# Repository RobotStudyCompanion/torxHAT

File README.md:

# torxHat

This repository contains the PCB design files for **torxHat**, designed in KiCAD, for the Robotic Study Companion (RSC; [rsc.ee](https://rsc.ee/)).
TorxHAT's design helps reduce dependency on any single specific Raspberry Pi audio HAT by supporting a wider variety. 
TorxHAT features USB Power Delivery and peripheral connectivity, including UART, multi channel PWM, I2C via Qwiic connector complete with a pass-through GPIO right-angle header.

Revision B Preview:

Pending validation testing; PCB in fabrication.

---

## Design Summary

A single USB-C PD input powers torxHAT, configured for 9V to 15V at up to 3A.
TorxHAT relies on two [LMR60440 3V to 36V, 4A, Synchronous, Buck Converters (link to datasheet)](https://www.ti.com/lit/ds/symlink/lmr60440.pdf?ts=1761834057549) powering two independent 5.1 V rails:

1. Logic rail: Raspberry Pi, audio hardware, and display
2. High-current rail for noisier peripherals: both servos, arcade button's LED plus an [Adafruit neopxLED ring (link to product page)](https://www.adafruit.com/product/2856)

TorxHAT's PCB packs a compact four-layer Raspberry Pi HAT-compatible design (though no EEPROM) with a complete pass-through GPIO connectivity intended for audio HATs.

We looked at the pinouts of following audio HATs when designing torxHAT:
* [Seeed Studios ReSpeaker 2-Mics pHAT v1.2(pinout link)](https://pinout.xyz/pinout/respeaker_2_mics_phat)
* [Waveshare WM8960 Audio HAT (product link)](https://www.waveshare.com/wm8960-audio-hat.htm)
* [Whisplay HAT(product link)](https://www.pisugar.com/products/whisplay-hat-for-pi-zero-2w-audio-display)
* [Adafruit Voice Bonnet (EOL; product link)](https://www.adafruit.com/product/4757)  
* [Google AIY Voice Bonnet v2 (EOL; pinout link)](https://pinout.xyz/pinout/aiy_voice_bonnet)
* [Google AIY Voice HAT v1 (EOL; pinout link)](https://pinout.xyz/pinout/voice_hat)

---

## Authors

* **RevA**: Raiko Torga
  * Original Bachelor's thesis artefact contribution. 
  * Supervisors: Matevž Borjan Zorec and Farnaz Baksh

* **RevB**: Raiko Torga, Matevž Borjan Zorec  

© Robot Study Companion 2026

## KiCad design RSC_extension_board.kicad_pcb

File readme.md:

# torxHat

This repository contains the PCB design files for **torxHat** developed for the Robotic Study Companion (RSC) platform.

This board was designed to reduce dependency on specific audio HATs, while supporting multiple audio HAT options it also offers USB power delivery and peripheral connectivity.

---

## Design Summary
The PCB was designed in KiCad.

The board is powered from a single USB-C PD input configured for 20 V 2.5 A.

Power distribution is split into two independent 5.1 V rails:

* Logic rail for Raspberry Pi, audio hardware, and display
* High-current rail for servos and LED ring

The PCB is a compact two-layer Raspberry Pi HAT-compatible design with pass-through GPIO connectivity intended for audio HATs.

Audio HATs considered:

* AIY Voice Bonnet  
* ReSpeaker 2 Mics pHAT  
* WM8960 Audio HAT  
* AIY Voice HAT  
* Adafruit Voice Bonnet  
* Whisplay HAT  

---

## Author

Raiko Torga

University of Tartu

Robotic Study Companion

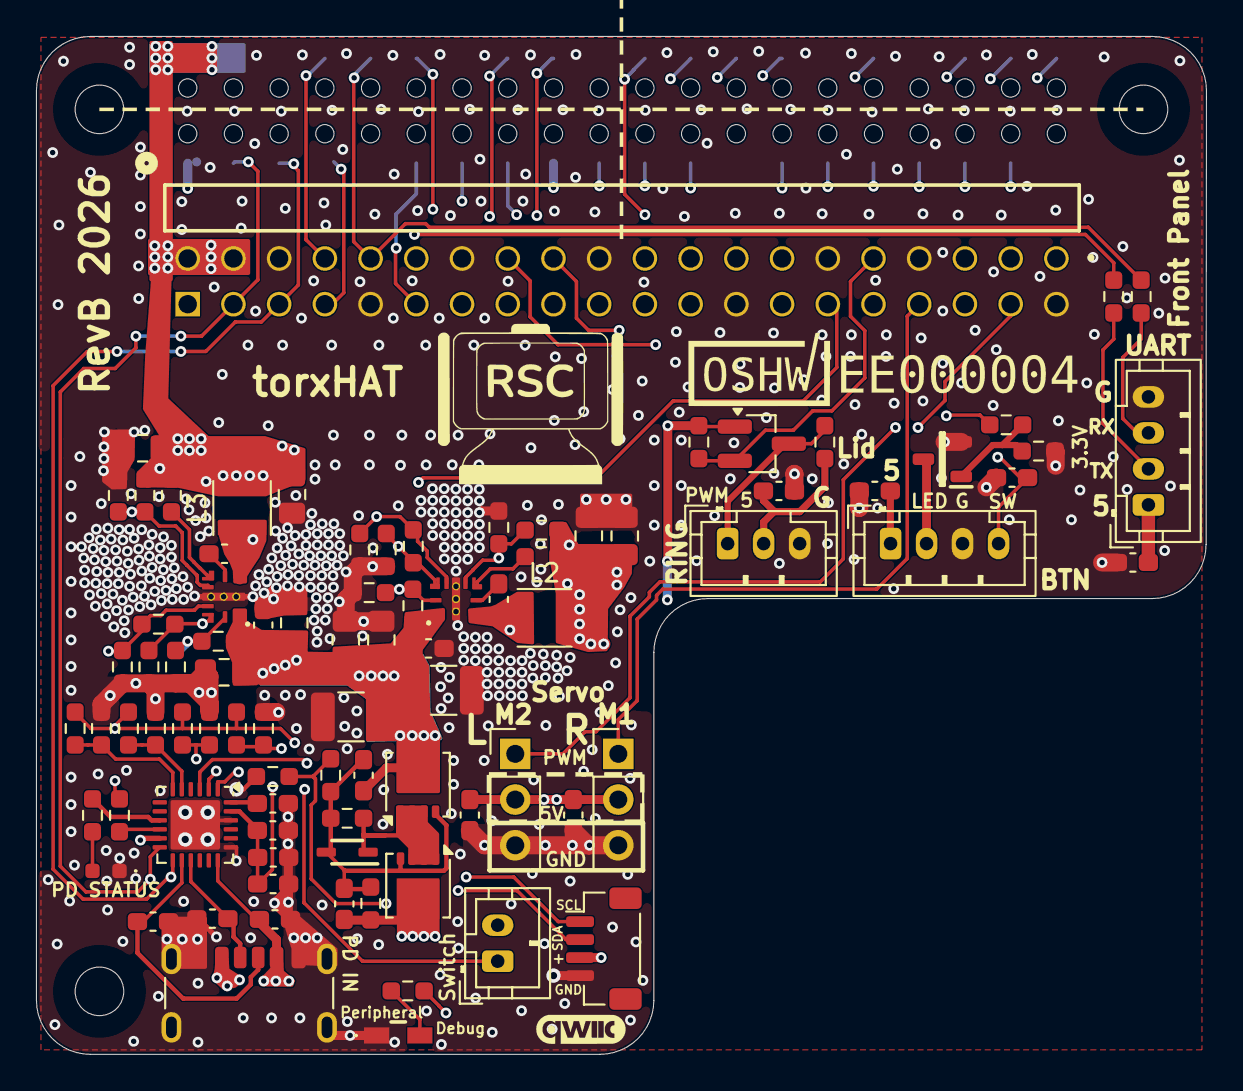
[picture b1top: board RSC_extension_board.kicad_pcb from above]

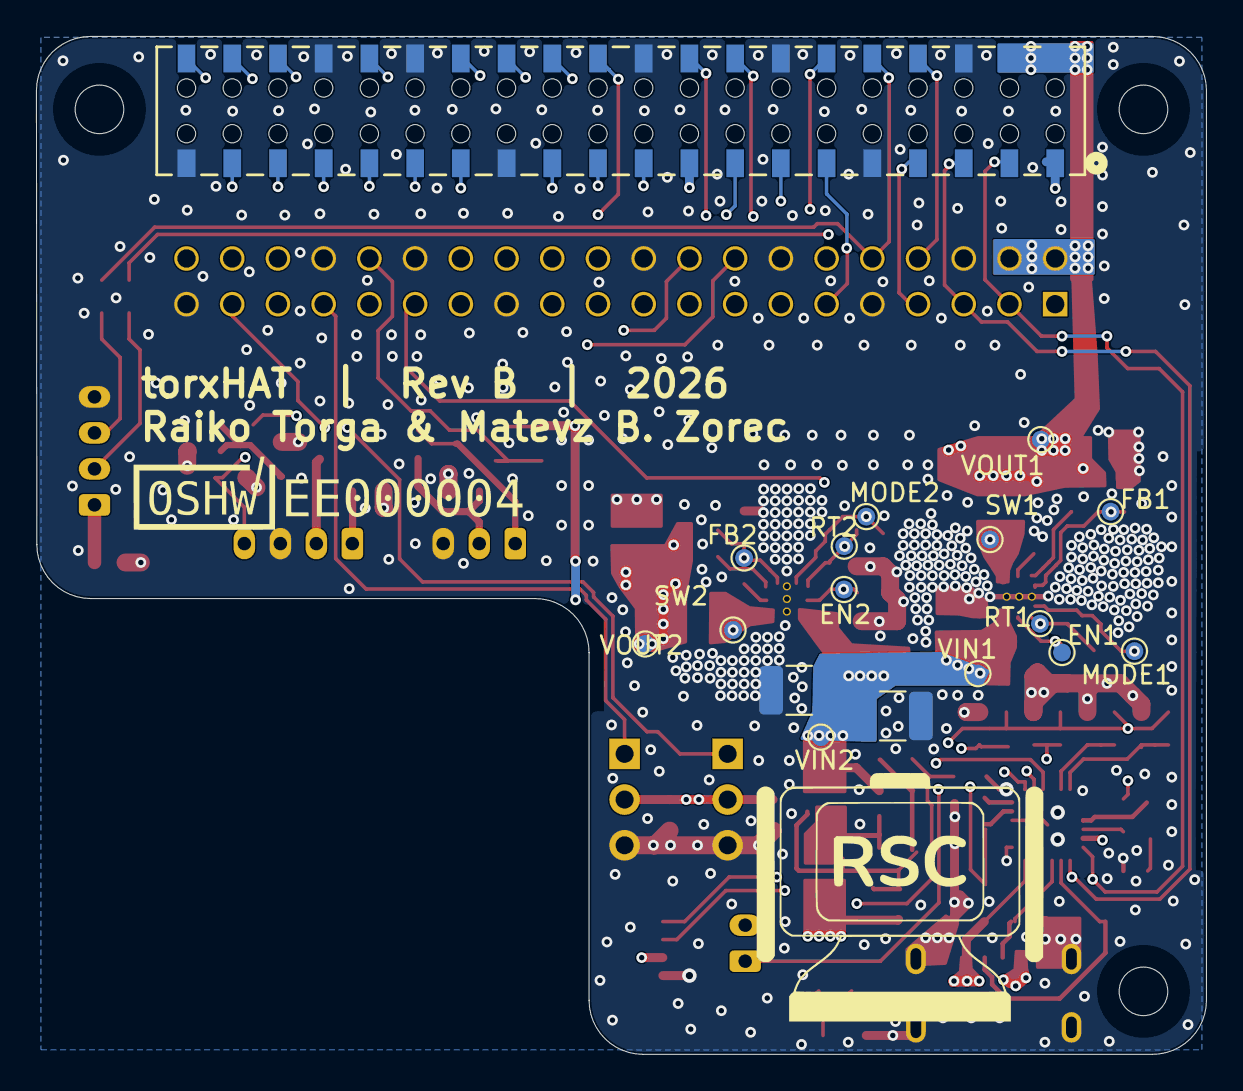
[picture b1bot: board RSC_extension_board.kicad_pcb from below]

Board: 4 copper layers, 65.0 x 56.5 mm, 105 parts (17 on the bottom side), 68 nets.

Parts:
C1, C2, C5, C6, C7, C8, C41, C42, C43, C44, C53, C54: 100nF; C_0603_1608Metric_Pad1.08x0.95mm_HandSolder
C37, C38, C39, C40: 4.7uF; C_0805_2012Metric_Pad1.18x1.45mm_HandSolder
C45, C46, C57, C58: 22uF; C_0805_2012Metric_Pad1.18x1.45mm_HandSolder
C47, C49: 390pF; C_0603_1608Metric_Pad1.08x0.95mm_HandSolder
C48: 3.3uF; C_0603_1608Metric_Pad1.08x0.95mm_HandSolder
C50, C51, C52, C55: 1uF; C_0603_1608Metric_Pad1.08x0.95mm_HandSolder
C56, C59, C60, C61: 22uF; C_1210_3225Metric_Pad1.33x2.70mm_HandSolder
D1: BAT54WS-7-F; SOD2513X120N
FPWM1, FPWM2: SHUNT; R_0603_1608Metric_Pad0.98x0.95mm_HandSolder
G1: qwiic_Logo; qwiic_5mm
J1: NPTC202KFMS-RC; CONN_NPTC202KFMS-RC_SUL
J2: Conn_01x03; JST_PH_B3B-PH-K_1x03_P2.00mm_Vertical
J3, J10: Conn_01x04; JST_PH_B4B-PH-K_1x04_P2.00mm_Vertical
J4: HTSW-120-25-L-D-RA; SAMTEC_HTSW-120-25-L-D-RA
J5: Conn_01x02; JST_PH_B2B-PH-K_1x02_P2.00mm_Vertical
J7, J8: Conn_01x03; PinHeader_1x03_P2.54mm_Vertical
J9: BM04B-SRSS; JST_SH_BM04B-SRSS-TB_1x04-1MP_P1.00mm_Vertical
J16: USB_C_Receptacle_PowerOnly_6P; USB_C_Receptacle_GCT_USB4125-xx-x-0190_6P_TopMnt_Horizontal
L2, L3: 1.5uH; L_Taiyo-Yuden_MD-3030
LED1: LW Y1SG-BFOO-GKJM-1; LWY1SGBFOOGKJM1
LED2: KR_EELP41.22-Q1S1-36-A8J8-020-R18; KREELP4122Q1S136A8J8020R18
PFM1, PFM2: DNP; R_0603_1608Metric_Pad0.98x0.95mm_HandSolder
Q1: 2N7002-7-F; SOT96P240X120-3N
Q2: BSS138; SOT-23_Handsoldering
Q3, Q4: DMP3013SFV; Diodes_PowerDI3333-8
R1, R10, R11, R22, R23: 1k; R_0603_1608Metric_Pad0.98x0.95mm_HandSolder
R2, R17: 150; R_0603_1608Metric_Pad0.98x0.95mm_HandSolder
R3, R4, R8: 10k; R_0603_1608Metric_Pad0.98x0.95mm_HandSolder
R5, R6, R7, R21: 100k; R_0603_1608Metric_Pad0.98x0.95mm_HandSolder
R9, R12, R13: 5.1k; R_0603_1608Metric_Pad0.98x0.95mm_HandSolder
R14, R20: 49k9; R_0603_1608Metric_Pad0.98x0.95mm_HandSolder
R15, R18: 5k1; R_0603_1608Metric_Pad0.98x0.95mm_HandSolder
R16, R19: 2k4; R_0603_1608Metric_Pad0.98x0.95mm_HandSolder
RENB1: DNP; R_0603_1608Metric_Pad0.98x0.95mm_HandSolder
RENB2: 100k; R_0603_1608Metric_Pad0.98x0.95mm_HandSolder
RENT1, RENT2: SHUNT; R_0603_1608Metric_Pad0.98x0.95mm_HandSolder
RFBB1, RFBB2: 20k; R_0603_1608Metric_Pad0.98x0.95mm_HandSolder
RFBT1, RFBT2: 82k; R_0603_1608Metric_Pad0.98x0.95mm_HandSolder
RT1, RT2: 16k5; R_0603_1608Metric_Pad0.98x0.95mm_HandSolder
TP1: EN1; TestPoint_Pad_D1.0mm
TP2: EN2; TestPoint_Pad_D1.0mm
TP3: VIN1; TestPoint_Pad_D1.0mm
TP4: MODE1; TestPoint_Pad_D1.0mm
TP5: VIN2; TestPoint_Pad_D1.0mm
TP6: MODE2; TestPoint_Pad_D1.0mm
TP7: RT1; TestPoint_Pad_D1.0mm
TP8: RT2; TestPoint_Pad_D1.0mm
TP11: SW1; TestPoint_Pad_D1.0mm
TP12: SW2; TestPoint_Pad_D1.0mm
TP13: FB1; TestPoint_Pad_D1.0mm
TP14: FB2; TestPoint_Pad_D1.0mm
TP15: VOUT1; TestPoint_Pad_D1.0mm
TP16: VOUT2; TestPoint_Pad_D1.0mm
U3, U4: LMR604403SRAKR; QFN-9_2.5x2.0mm_RAK
U5: CYPD3177-24LQ; QFN-24-1EP_4x4mm_P0.5mm_EP2.75x2.75mm

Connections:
+3.3V: J1.1, J1.17, J4.01, J4.17, J9.3, Q2.1 (G), R3.1
+3.3V_PD: C52.2, C53.2, C54.2, R9.2, R12.2, R15.2, R18.2, R20.2, U5.23 (VDDD)
+5V_RPI: C7.1, C45.1, C58.1, J1.2, J1.4, J4.02, J4.04, J10.1, L3.2, R5.2, RFBT1.1, TP15.1 (1_1)
+5V_Servo: C2.2, C5.1, C6.1, C8.1, C46.1, C57.1, J2.2, J3.1, J7.2, J8.2, L2.2, R1.2, R4.1, R6.2, RFBT2.1, TP16.1 (1_1)
/BUTTON: C1.2, J1.16, J3.4, J4.16
/BUTTON_LED: J3.2, Q1.3 (D)
/GPIO00: J1.27, J4.27
/GPIO01: J1.28, J4.28
/GPIO06: J1.31, J4.31
/GPIO08: J1.24, J4.24
/GPIO16: J1.36, J4.36
/GPIO17: J1.11, J4.11
/GPIO25: J1.22, J4.22
/I2S_BCLK: J1.12, J4.12
/I2S_DIN: J1.38, J4.38
/I2S_DOUT: J1.40, J4.40
/I2S_LRCLK: J1.35, J4.35
/LCD_BL: J1.15, J4.15
/LED_3.3V: J1.32, J4.32, Q2.2 (S), R3.2
/LED_5V: J2.1, Q2.3 (D), R4.2
/LED_PWM: J1.18, J4.18, R2.2
/M1_PWM: J1.33, J4.33, J7.1
/M2_PWM: J1.37, J4.37, J8.1
/RX_3.3V: J1.10, J4.10, R23.2
/SCL: J1.5, J4.05, J9.1, U5.13 (HPI_SCL)
/SDA: J1.3, J4.03, J9.2, U5.12 (HPI_SDA)
/SERVO_EN: J1.29, J4.29, RENB2.1, RENT2.1, TP2.1 (1_1), U4.9 (EN)
/SPI_CLK: J1.23, J4.23
/SPI_CS: J1.26, J4.26
/SPI_DC: J1.13, J4.13
/SPI_MISO: J1.21, J4.21
/SPI_MOSI: J1.19, J4.19
/SPI_RST: J1.7, J4.07
/TX_3.3V: J1.8, J4.08, R22.2
GND: C1.1, C2.1, C5.2, C6.2, C7.2, C8.2, C37.2, C38.2, C39.2, C40.2, C41.2, C42.2, C45.2, C46.2, C47.1, C48.1, C49.1, C50.1, C52.1, C53.1, C54.1, C56.1, C57.2, C58.2, C59.1, C60.1, C61.1, J1.6, J1.9, J1.14, J1.20, J1.25, J1.30, J1.34, J1.39, J2.3, J3.3, J4.06, J4.09, J4.14, J4.20, J4.25, J4.30, J4.34, J4.39, J7.3, J8.3, J9.4, J10.4, J16.A12 (GND), J16.B12 (GND), J16.S1 (SHIELD), LED1.1 (K), LED2.1 (K), PFM1.2, PFM2.2, Q1.2 (S), R7.1, R10.1, R13.1, R16.1, R19.1, R21.2, RENB1.2, RENB2.2, RFBB1.2, RFBB2.2, RT1.2, RT2.2, U3.2 (PGND), U4.2 (PGND), U5.19 (GND), U5.22 (GND), U5.25 (GND)
unnamed: C51.1, C55.1, D1.2 (A), Q3.4 (G), Q4.4 (G), R8.1, R11.2, R14.1
unnamed: D1.1 (K), Q3.1 (S), Q3.2 (S), Q3.3 (S), Q4.1 (S), Q4.2 (S), Q4.3 (S), R14.2
unnamed: J5.1, U5.3 (VBUS_FET_EN)
unnamed: J5.2, R7.2, R11.1
unnamed: J10.2, R22.1
unnamed: J10.3, R23.1
unnamed: C49.2, J16.A5 (CC1), U5.15 (CC1)
unnamed: C47.2, J16.B5 (CC2), U5.14 (CC2)
unnamed: LED1.2 (A), R1.1
unnamed: LED2.2 (A), R17.1
unnamed: Q1.1 (G), R2.1, R21.1
unnamed: C48.2, C51.2, J16.A9 (VBUS), J16.B9 (VBUS), Q3.5 (D), R8.2, U5.18 (VBUS_IN)
unnamed: C43.1, U3.4 (BOOT)
unnamed: RENB1.1, RENT1.1, TP1.1 (1_1), U3.9 (EN)
unnamed: RFBB1.1, RFBT1.2, TP13.1 (1_1), U3.6 (FB)
unnamed: FPWM1.1, PFM1.1, TP4.1 (1_1), U3.7 (MODE/SYNC)
unnamed: R5.1, U3.5 (PG)
unnamed: FPWM1.2, RT1.1, TP7.1 (1_1), U3.8 (RT)
unnamed: C43.2, L3.1, TP11.1 (1_1), U3.3 (SW)
unnamed: C44.1, U4.4 (BOOT)
unnamed: RFBB2.1, RFBT2.2, TP14.1 (1_1), U4.6 (FB)
unnamed: FPWM2.1, PFM2.1, TP6.1 (1_1), U4.7 (MODE/SYNC)
unnamed: R6.1, U4.5 (PG)
unnamed: FPWM2.2, RT2.1, TP8.1 (1_1), U4.8 (RT)
unnamed: C44.2, L2.1, TP12.1 (1_1), U4.3 (SW)
unnamed: R17.2, U5.9 (FAULT)
unnamed: R20.1, U5.10 (FLIP)
unnamed: R15.1, R16.2, U5.5 (ISNK_COARSE)
unnamed: R18.1, R19.2, U5.6 (ISNK_FINE)
unnamed: R9.1, R10.2, U5.2 (VBUS_MAX)
unnamed: R12.1, R13.2, U5.1 (VBUS_MIN)
unnamed: C50.2, U5.24 (VCCD)
VBUS: C37.1, C38.1, C39.1, C40.1, C41.1, C42.1, C55.2, C56.2, C59.2, C60.2, C61.2, Q4.5 (D), RENT1.2, RENT2.2, TP3.1 (1_1), TP5.1 (1_1), U3.1 (VIN), U4.1 (VIN), U5.11 (VDC_OUT)

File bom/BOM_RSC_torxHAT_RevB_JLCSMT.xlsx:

Comment | Designator | Footprint | JLCPCB Part #（optional）
100nF | C1, C2, C5, C6, C7, C8, C41, C42, C43, C44, C53, C54 | C_0603_1608Metric_Pad1.08x0.95mm_HandSolder | C1591
4.7uF | C37, C38, C39, C40 | C_0805_2012Metric_Pad1.18x1.45mm_HandSolder | C5159426
22uF | C45, C46, C57, C58 | C_0805_2012Metric_Pad1.18x1.45mm_HandSolder | C53133025
390pF | C47, C49 | C_0603_1608Metric_Pad1.08x0.95mm_HandSolder | C1617
3.3uF | C48 | C_0603_1608Metric_Pad1.08x0.95mm_HandSolder | C342962
1uF | C50, C51, C52, C55 | C_0603_1608Metric_Pad1.08x0.95mm_HandSolder | C5199872
22uF | C56, C59, C60, C61 | C_1210_3225Metric_Pad1.33x2.70mm_HandSolder | C386098
BAT54WS-7-F | D1 | SOD2513X120N | C42419960
USB_C_Receptacle_PowerOnly_6P | J16 | USB_C_Receptacle_GCT_USB4125-xx-x-0190_6P_TopMnt_Horizontal | C5407555
LW Y1SG-BFOO-GKJM-1 | LED1 | LWY1SGBFOOGKJM1 | C29549378
KR_EELP41.22-Q1S1-36-A8J8-020-R18 | LED2 | KREELP4122Q1S136A8J8020R18 | C39534692
2N7002-7-F | Q1 | SOT96P240X120-3N | C85049
BSS138 | Q2 | SOT-23_Handsoldering | C52895
DMP3013SFV | Q3, Q4 | Diodes_PowerDI3333-8 | C264098
1k | R1, R10, R11, R22, R23 | R_0603_1608Metric_Pad0.98x0.95mm_HandSolder | C2907002
150 | R2, R17 | R_0603_1608Metric_Pad0.98x0.95mm_HandSolder | C2906994
10k | R3, R4, R8 | R_0603_1608Metric_Pad0.98x0.95mm_HandSolder | C101254
100k | R5, R6, R7, R21, RENB2 | R_0603_1608Metric_Pad0.98x0.95mm_HandSolder | C54973939
5k1 | R9, R12, R13, R15, R18 | R_0603_1608Metric_Pad0.98x0.95mm_HandSolder | C54973944
49k9 | R14, R20 | R_0603_1608Metric_Pad0.98x0.95mm_HandSolder | C304759
2k4 | R16, R19 | R_0603_1608Metric_Pad0.98x0.95mm_HandSolder | C54920893
20k | RFBB1, RFBB2 | R_0603_1608Metric_Pad0.98x0.95mm_HandSolder | C54973936
82k | RFBT1, RFBT2 | R_0603_1608Metric_Pad0.98x0.95mm_HandSolder | C54921082
16k5 | RT1, RT2 | R_0603_1608Metric_Pad0.98x0.95mm_HandSolder | C22812
CYPD3177-24LQ | U5 | QFN-24-1EP_4x4mm_P0.5mm_EP2.75x2.75mm | C2959321

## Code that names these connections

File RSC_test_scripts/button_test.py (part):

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"""Button + LED test rig for the RSC front panel.

BUTTON  (GPIO23) idles low, goes high on press.
LED_PWM (GPIO24) drives the arcade button's LED through Q1.
RING    (GPIO12) drives 16x SKC6812 RGBW NeoPixel ring via J6.
"""

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LED_PIN     = 24
BOUNCE_TIME = 0.05
HOLD_TIME   = 1
RING_PIN    = board.D12   # M1_PWM via J6 servo connector
RING_COUNT  = 16          # SKC6812 RGBW 16-pixel ring

SERVO_PINS  = [13, 26]    # M2_PWM (J7/left), M3_PWM (J8/right)
SERVO_STOP  = 1500        # µs — neutral

SERVO_R_TRIM = 105   # µs — increase to speed up right, decrease to slow it down
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
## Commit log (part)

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2025-11-04 changed raspberry connector footprint to https://ee.farnell.com/harwin/m20-7812045/connector-rcpt-40pos-2-54mm-2row/dp/3225919
2025-11-04 added .stp file for raspi connector
2025-11-05 added cc resistors
2025-11-05 added some tvs diodes. symbols weird
2025-11-05 updated symbol
2025-11-05 some external power stuff
2025-11-09 bit of power circuit
2025-11-09 updated fuse
2025-11-09 save
2025-11-12 qwiic connector and 3.3v led out
2025-11-12 new tvs diodes
2025-11-12 added power LED
2025-11-18 added possibility for button led dimming
2025-11-19 started possible voice schematic
2025-11-20 bit of voice schematic
2025-11-20 voice schematic
2025-11-20 voice schematic switch, 3d files
2025-11-27 a4 to a3
2025-12-03 some new pins for raspberry gpio-s
2025-12-03 Led_3.3 has also net
2025-12-14 new power switch, added spi out
2025-12-15 added power for spi
2025-12-17 spi display pinout change. button connector simplified.
2025-12-17 new cs pin
2025-12-22 started designing pd in
2025-12-22 20v 2a PD input
2025-12-23 started 20v to 5v schematic
2025-12-28 buck converter
2026-01-03 some new ideas for power
2026-01-04 started new buck
2026-01-05 new buck
2026-01-06 annotation and pcb outline
2026-01-06 new caps and bit of layout
2026-01-07 layout- 1st placement
2026-01-07 new bottom layer footprint for Pi connector
2026-01-07 rounded edges, new rules
2026-01-07 added fuze
2026-01-09 added pi and piZero(or voice hat) outlines
2026-01-10 new connectors placement
2026-01-14 20v in
2026-01-19 20v to 5v 4A times two
2026-01-19 new mounting holes
2026-01-21 buck converter test pads and optional resistors
2026-01-25 some footprint for LMR60440
2026-01-26 experimental 2x20 out for voice hat
2026-01-28 pd controller
2026-01-28 DMP3013's for pd controller
2026-01-28 playing around with 2x20 pin. no 3d on top one
2026-01-28 3d model for 90deg smd header
2026-02-01 bit of placement and started routing
2026-02-02 bit more routing
2026-02-03 L shaped layout. voice pins pushed inwards
2026-02-04 some changes
2026-02-05 experimental thermal pads on bottom side. pins for on/off switch.
2026-02-09 bit of layout. new LMR60440 footprint
2026-02-11 bit of routing
2026-02-11 spi connector pin order. bit of routing
2026-02-12 new placement for buck converters
2026-02-12 user.drawing has L shaped edge.cut version
2026-02-14 all nets for headers
2026-02-16 smaller test pads. some routing
2026-02-17 routing fixes
2026-02-24 bit wider power tracks
2026-02-25 L shaped edge cut. PD controller and servo connectors got moved bit left
2026-02-25 pull down resistor on PD mosfet gates- for jumper
2026-03-01 bit better gnd plane. some silkscreen
2026-03-01 test pads on board. gnd vias for islands
2026-03-03 better gnd plane
2026-03-03 gnd plane better
2026-03-04 silkscreen: logo, text, testpads.
2026-03-04 some drc fixes
2026-03-04 edge cut line width
2026-03-04 fixed drc errors.
2026-03-05 re push
2026-03-11 removed unnecessary mounting hole
2026-03-15 some fixes with vias
2026-03-16 vias not on pads. PD controller slightly lower
2026-03-25 repour and drc before gerber files
2026-03-26 generic 2.54mm headers and testPads excluded from BOM
2026-04-14 J4 connector had correct footprint but false component name
2026-04-30 rule areas
2026-04-30 added title box information
2026-05-06 added author to title box
2026-05-18 added reference to the voice sch
2026-05-19 correct feedback resistors on buck converters
2026-05-19 readme and 3d view image
2026-05-20 add license
2026-06-01 Started Rev B: white power LED, USB slightly over edge
2026-06-02 new logo. lmr has 1st pin marking. pinout on silkscreen.
2026-06-17 silkscreen: torxhat, OSHW Certification Mark
2026-06-18 1k led resistors. top silkscreen

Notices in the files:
README.md:
Licensed under CERN-OHL-W v2
